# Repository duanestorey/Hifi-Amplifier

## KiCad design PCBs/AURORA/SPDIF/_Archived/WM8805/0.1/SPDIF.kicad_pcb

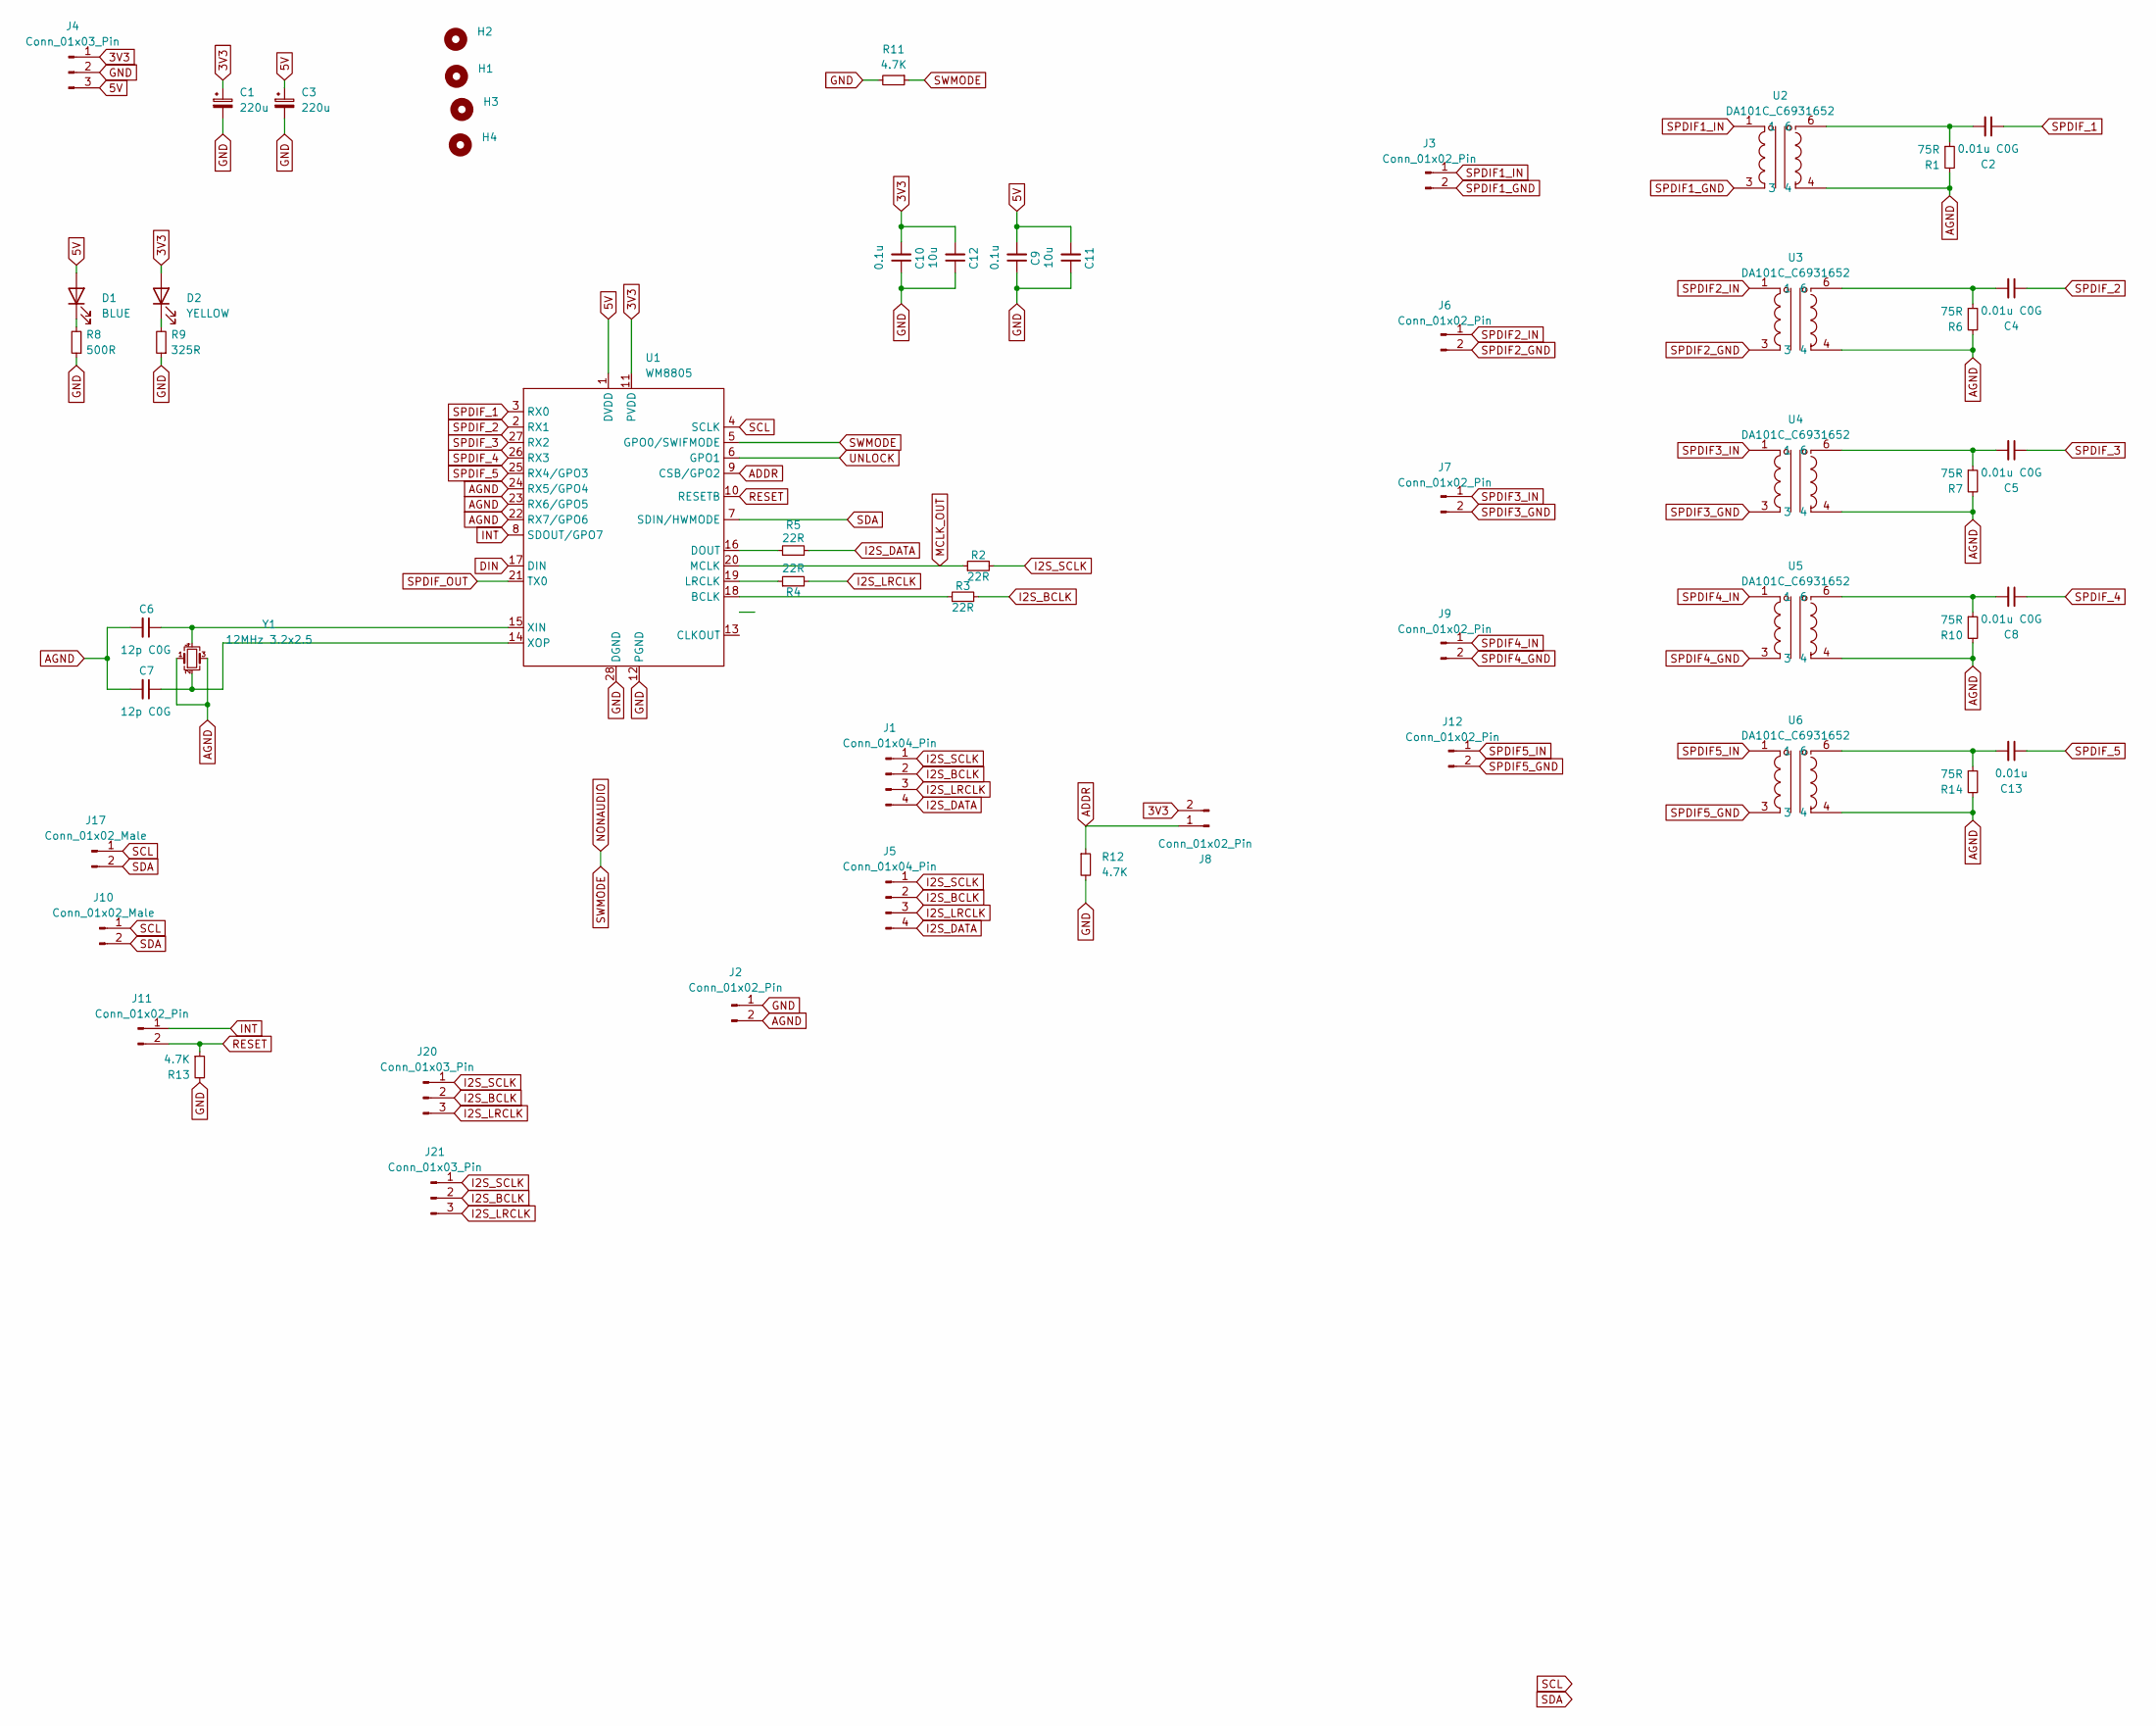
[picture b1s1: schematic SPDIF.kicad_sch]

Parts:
C1, C3: 220u; CP_Radial_D6.3mm_P2.50mm
C2, C4, C5, C8: 0.01u C0G; C_0805_2012Metric_Pad1.18x1.45mm_HandSolder; Mouser 791-0805N103G250CT
C6, C7: 12p C0G; C_0805_2012Metric_Pad1.18x1.45mm_HandSolder; Mouser 603-CC805FRNPO9BN120
C9, C10: 0.1u; C_0805_2012Metric_Pad1.18x1.45mm_HandSolder
C11, C12: 10u; C_1206_3216Metric_Pad1.33x1.80mm_HandSolder
C13: 0.01u; C_0805_2012Metric_Pad1.18x1.45mm_HandSolder; Mouser C0G
D1: BLUE; LED_0805_2012Metric_Pad1.15x1.40mm_HandSolder
D2: YELLOW; LED_0805_2012Metric_Pad1.15x1.40mm_HandSolder
H1, H2, H3, H4: MountingHole; MountingHole_3.2mm_M3_DIN965_Pad_TopOnly
J1: Conn_01x04_Pin; JST_PH_B4B-PH-K_1x04_P2.00mm_Vertical
J2, J8: Conn_01x02_Pin; PinHeader_1x02_P2.54mm_Vertical
J3, J6, J7, J9, J12: Conn_01x02_Pin; JST_XH_B2B-XH-A_1x02_P2.50mm_Vertical
J4, J20, J21: Conn_01x03_Pin; JST_PH_B3B-PH-K_1x03_P2.00mm_Vertical
J5: Conn_01x04_Pin; PinHeader_1x04_P2.54mm_Vertical
J10, J17: Conn_01x02_Male; JST_PH_B2B-PH-K_1x02_P2.00mm_Vertical
J11: Conn_01x02_Pin; JST_PH_B2B-PH-K_1x02_P2.00mm_Vertical
R1, R6, R7, R10, R14: 75R; R_0603_1608Metric_Pad0.98x0.95mm_HandSolder; Mouser 71-CRCW0603-75-E3
R2, R3, R4, R5: 22R; R_0805_2012Metric_Pad1.20x1.40mm_HandSolder
R8: 500R; R_0603_1608Metric_Pad0.98x0.95mm_HandSolder
R9: 325R; R_0603_1608Metric_Pad0.98x0.95mm_HandSolder
R11, R12, R13: 4.7K; R_0603_1608Metric_Pad0.98x0.95mm_HandSolder
U1: WM8805; SSOP-28_5.3x10.2mm_P0.65mm
U2, U3, U4, U5, U6: DA101C_C6931652; XFMR-TH_4P-L9.5-W9.0-P5.08-LS10.2_C9900096976; LCSC Part C6931652
Y1: 12MHz 3.2x2.5; Crystal_SMD_SeikoEpson_FA238-4Pin_3.2x2.5mm; Mouser 520-120-8-33B2CKMTR3

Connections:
3V3: C1.1, C10.2, C12.2, D2.2 (A), J4.1, J8.2, U1.11 (PVDD)
5V: C3.1, C9.2, C11.2, D1.2 (A), J4.3, U1.1 (DVDD)
ADDR: J8.1, R12.1, U1.9 (CSB/GPO2)
AGND: C6.2, C7.2, J2.2, R1.2, R6.2, R7.2, R10.2, R14.2, U1.22 (RX7/GPO6), U1.23 (RX6/GPO5), U1.24 (RX5/GPO4), U2.4, U3.4, U4.4, U5.4, U6.4, Y1.1, Y1.3
DIN: U1.17 (DIN)
GND: C1.2, C3.2, C9.1, C10.1, C11.1, C12.1, J2.1, J4.2, R8.1, R9.1, R11.2, R12.2, R13.2, U1.12 (PGND), U1.28 (DGND)
I2S_BCLK: J1.2, J5.2, J20.2, J21.2, R3.2
I2S_DATA: J1.4, J5.4, R5.2
I2S_LRCLK: J1.3, J5.3, J20.3, J21.3, R4.2
I2S_SCLK: J1.1, J5.1, J20.1, J21.1, R2.2
INT: J11.1, U1.8 (SDOUT/GPO7)
MCLK_OUT: R2.1, U1.20 (MCLK)
NONAUDIO: R11.1, U1.5 (GPO0/SWIFMODE)
unnamed: C2.2, R1.1, U2.6
unnamed: C4.2, R6.1, U3.6
unnamed: C5.2, R7.1, U4.6
unnamed: C8.2, R10.1, U5.6
unnamed: C13.2, R14.1, U6.6
unnamed: D1.1 (K), R8.2
unnamed: D2.1 (K), R9.2
unnamed: R3.1, U1.18 (BCLK)
unnamed: R5.1, U1.16 (DOUT)
unnamed: R4.1, U1.19 (LRCLK)
unnamed: C6.1, U1.15 (XIN), Y1.4
unnamed: C7.1, U1.14 (XOP), Y1.2
RESET: J11.2, R13.1, U1.10 (RESETB)
SCL: J10.1, J17.1, U1.4 (SCLK)
SDA: J10.2, J17.2, U1.7 (SDIN/HWMODE)
SPDIF1_GND: J3.2, U2.3
SPDIF1_IN: J3.1, U2.1
SPDIF2_GND: J6.2, U3.3
SPDIF2_IN: J6.1, U3.1
SPDIF3_GND: J7.2, U4.3
SPDIF3_IN: J7.1, U4.1
SPDIF4_GND: J9.2, U5.3
SPDIF4_IN: J9.1, U5.1
SPDIF5_GND: J12.2, U6.3
SPDIF5_IN: J12.1, U6.1
SPDIF_1: C2.1, U1.3 (RX0)
SPDIF_2: C4.1, U1.2 (RX1)
SPDIF_3: C5.1, U1.27 (RX2)
SPDIF_4: C8.1, U1.26 (RX3)
SPDIF_5: C13.1, U1.25 (RX4/GPO3)
SPDIF_OUT: U1.21 (TX0)
UNLOCK: U1.6 (GPO1)

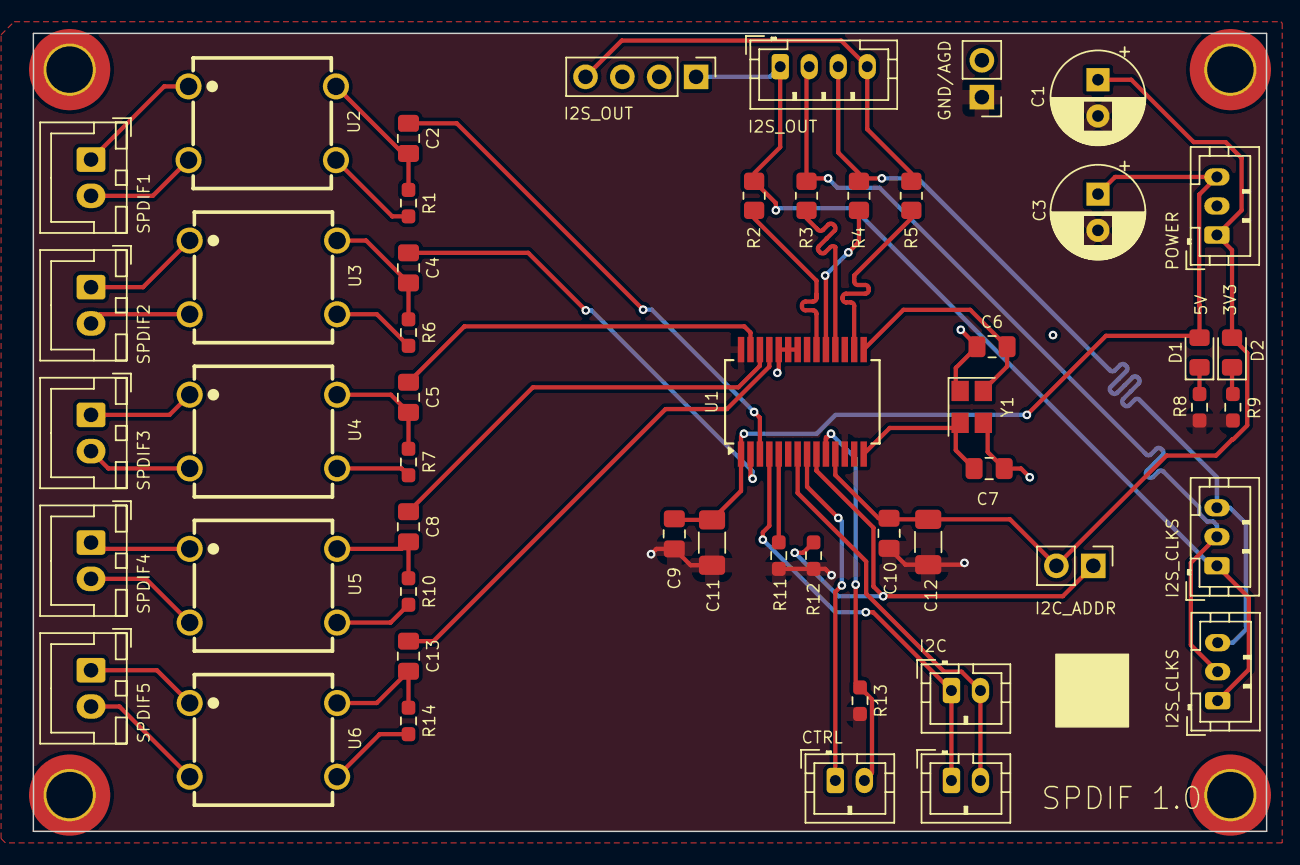
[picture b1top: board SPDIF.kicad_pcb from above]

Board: 4 copper layers, 85.0 x 55.0 mm, 55 parts (0 on the bottom side), 42 nets.

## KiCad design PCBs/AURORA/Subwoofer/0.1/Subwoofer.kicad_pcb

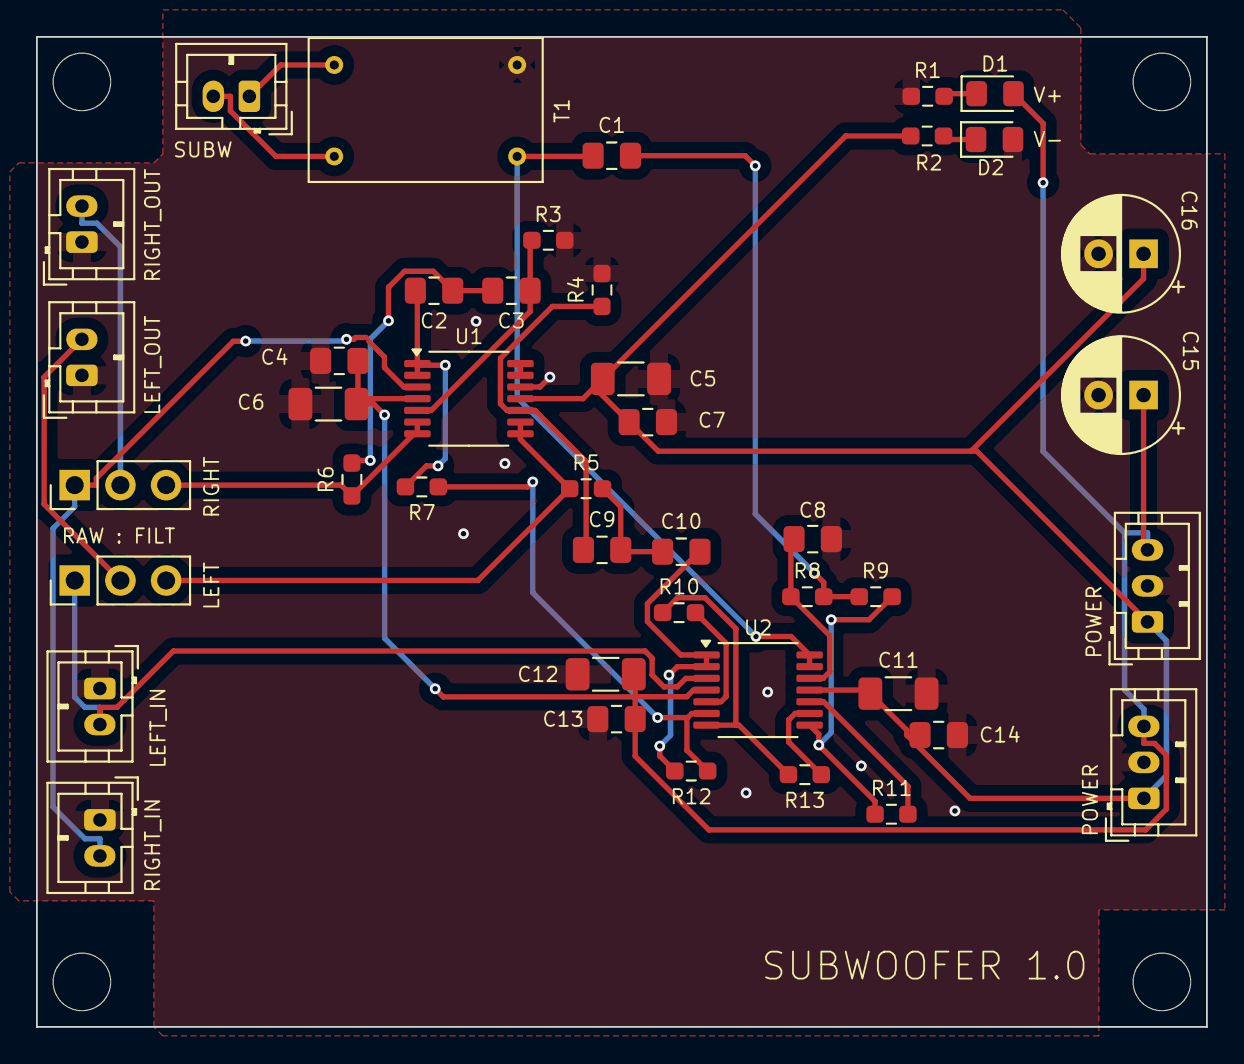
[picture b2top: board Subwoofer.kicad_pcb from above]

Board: 2 copper layers, 65.0 x 55.0 mm, 47 parts (0 on the bottom side), 29 nets.

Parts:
C1, C2, C3, C9, C10: 200N C0G; C_0805_2012Metric_Pad1.18x1.45mm_HandSolder
C4, C7, C13, C14: 0.1U; C_0805_2012Metric_Pad1.18x1.45mm_HandSolder
C5, C6, C11, C12: 10U; C_1206_3216Metric_Pad1.33x1.80mm_HandSolder
C8: 91N C0G; C_0805_2012Metric_Pad1.18x1.45mm_HandSolder
C15, C16: 470u; CP_Radial_D6.3mm_P2.50mm
D1: YELLOW; LED_0805_2012Metric_Pad1.15x1.40mm_HandSolder
D2: BLUE; LED_0805_2012Metric_Pad1.15x1.40mm_HandSolder
H1, H2, H3, H4: MountingHole; MountingHole_3.2mm_M3
J1, J2, J3, J7, J9: Conn_01x02_Pin; JST_PH_B2B-PH-K_1x02_P2.00mm_Vertical
J4, J5: Conn_01x03_Pin; PinHeader_1x03_P2.54mm_Vertical
J6, J8: Conn_01x03_Male; JST_PH_B3B-PH-K_1x03_P2.00mm_Vertical
R1: 1.25K; R_0603_1608Metric_Pad0.98x0.95mm_HandSolder
R2: 1K; R_0603_1608Metric_Pad0.98x0.95mm_HandSolder
R3, R4, R5, R6: 6.8K; R_0603_1608Metric_Pad0.98x0.95mm_HandSolder
R7: 25k; R_0603_1608Metric_Pad0.98x0.95mm_HandSolder
R8: 20K; R_0603_1608Metric_Pad0.98x0.95mm_HandSolder
R9: 11K; R_0603_1608Metric_Pad0.98x0.95mm_HandSolder
R10, R11, R12, R13: 25K; R_0603_1608Metric_Pad0.98x0.95mm_HandSolder
T1: Transformer_Audio; DA101C
U1, U2: Opamp_Quad; TSSOP-14_4.4x5mm_P0.65mm

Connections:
AGND: C4.2, C5.2, C6.2, C7.2, C8.1, C11.2, C12.2, C13.2, C14.2, C15.2, C16.2, D2.2 (A), J2.1, J3.1, J6.2, J7.1, J8.2, J9.1, R1.1, R3.2, R4.2, T1.2 (AB), U1.12 (+)
LEFT_FILT: J5.3, R5.1, U1.8, U1.9 (-)
LEFT_IN: J5.1, J7.2, U2.3 (+)
LEFT_OUT: J3.2, J5.2
unnamed: C1.2, R8.2, R9.1
unnamed: C2.1, C3.2, R6.2
unnamed: C9.2, C10.1, R5.2
unnamed: D1.1 (K), R1.2
unnamed: D2.1 (K), R2.2
unnamed: R10.1, R13.2, U2.7
unnamed: R9.2, R11.1, U2.8
unnamed: C2.2, R7.2, U1.1, U1.2 (-)
unnamed: C3.1, R3.1, U1.5 (+)
unnamed: C9.1, R4.1, U1.10 (+)
unnamed: U1.13 (-), U1.14
unnamed: C10.2, R12.2, U2.1, U2.2 (-)
unnamed: R10.2, U2.5 (+)
unnamed: R7.1, R12.1, U2.6 (-)
unnamed: R11.2, U2.10 (+)
unnamed: R13.1, U2.9 (-)
unnamed: C8.2, R8.1, U2.12 (+)
RIGHT_FILT: J4.3, R6.1, U1.6 (-), U1.7
RIGHT_IN: J4.1, J9.2, U1.3 (+)
RIGHT_OUT: J2.2, J4.2
SUBW: C1.1, T1.1 (AA), U2.13 (-), U2.14
SUBWN: J1.1, T1.3 (SA)
SUBWP: J1.2, T1.4 (SB)
V+: C4.1, C6.1, C12.1, C13.1, C15.1, D1.2 (A), J6.3, J8.3, U1.4 (V+), U2.4 (V+)
V-: C5.1, C7.1, C11.1, C14.1, C16.1, J6.1, J8.1, R2.1, U1.11 (V-), U2.11 (V-)

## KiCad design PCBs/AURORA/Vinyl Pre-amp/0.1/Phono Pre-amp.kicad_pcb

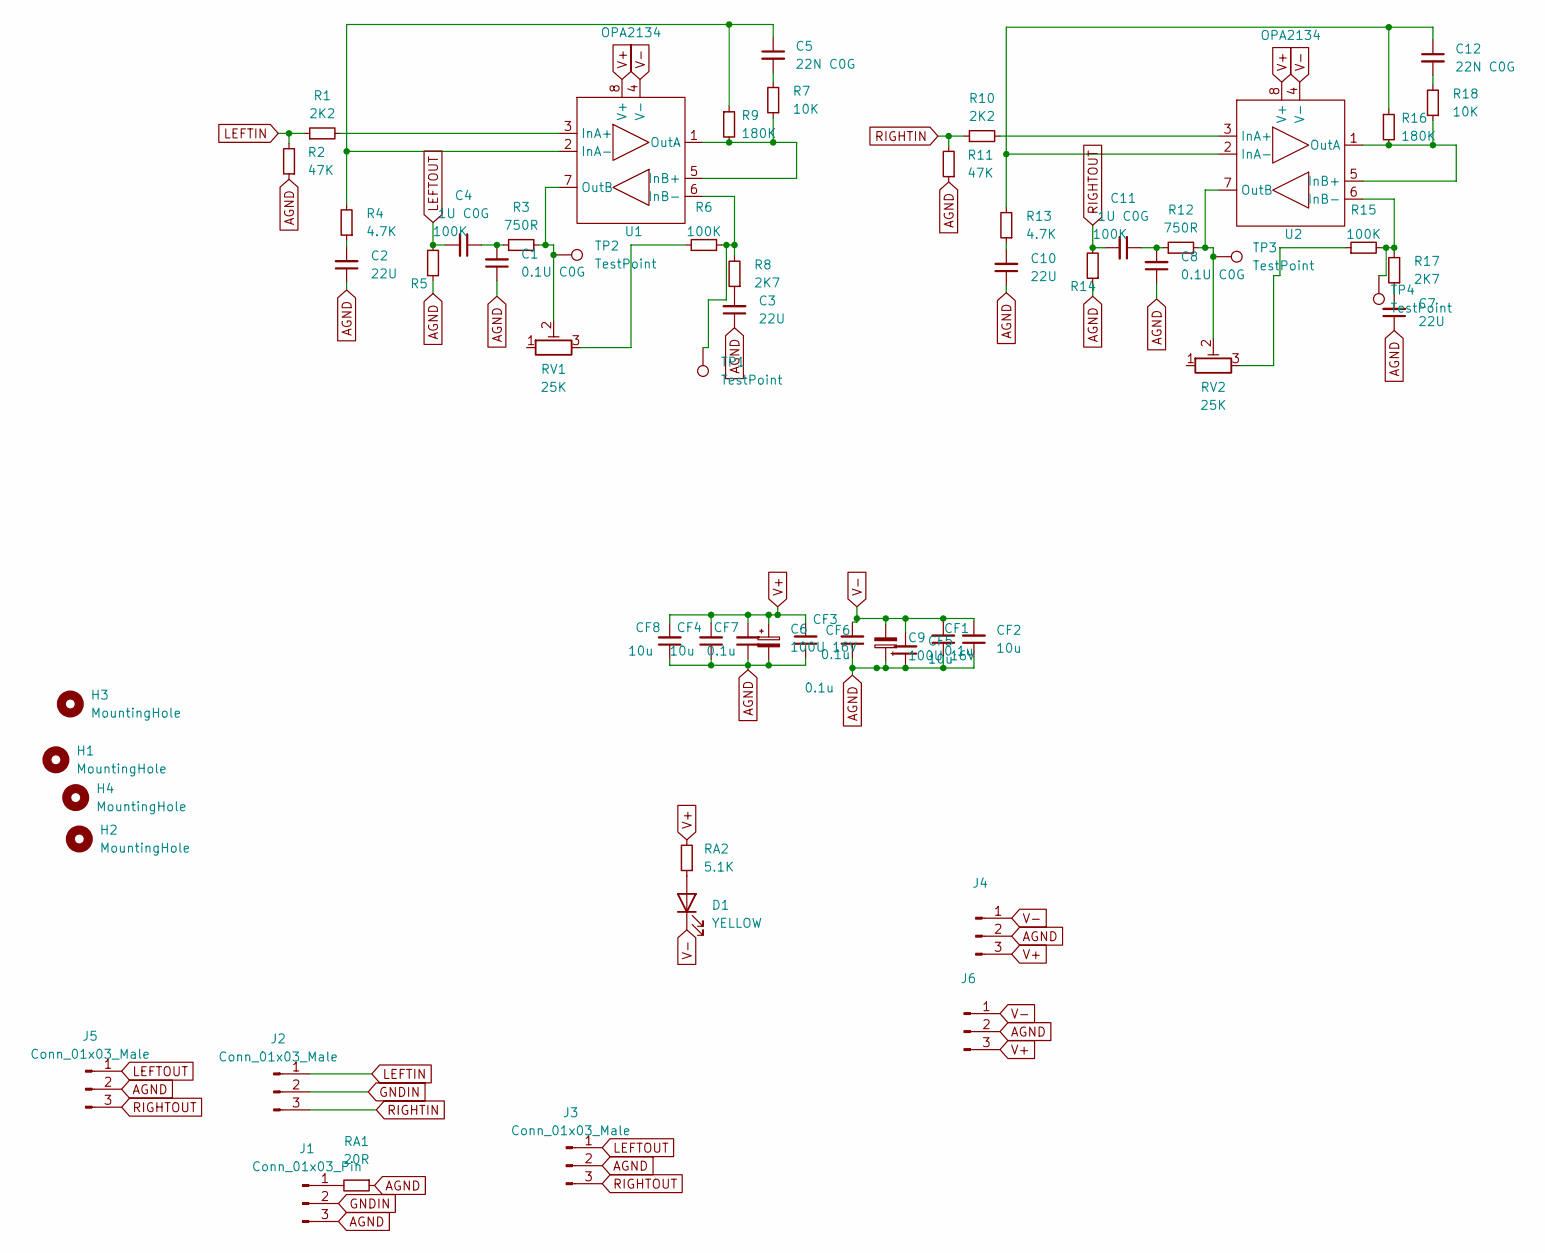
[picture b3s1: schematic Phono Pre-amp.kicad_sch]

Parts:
C1, C8: 0.1U C0G; C_1206_3216Metric_Pad1.33x1.80mm_HandSolder
C2, C3, C7, C10: 22U; CP_Radial_D6.3mm_P2.50mm
C4, C11: 1U C0G; C_Rect_L7.2mm_W11.0mm_P5.00mm_FKS2_FKP2_MKS2_MKP2
C5, C12: 22N C0G; C_0805_2012Metric_Pad1.18x1.45mm_HandSolder
C6, C9: 100U 16V; CP_Radial_D6.3mm_P2.50mm
CF1, CF3, CF6, CF7: 0.1u; C_0805_2012Metric_Pad1.18x1.45mm_HandSolder
CF2, CF4, CF5, CF8: 10u; C_1206_3216Metric_Pad1.33x1.80mm_HandSolder
D1: YELLOW; LED_0805_2012Metric_Pad1.15x1.40mm_HandSolder
H1, H2, H3, H4: MountingHole; MountingHole_3.2mm_M3
J1: Conn_01x03_Pin; PinHeader_1x03_P2.54mm_Vertical
J2, J4, J5, J6: Conn_01x03_Male; JST_PH_B3B-PH-K_1x03_P2.00mm_Vertical
J3: Conn_01x03_Male; PinHeader_1x03_P2.54mm_Vertical
R1, R10: 2K2; R_0805_2012Metric_Pad1.20x1.40mm_HandSolder
R2, R11: 47K; R_0805_2012Metric_Pad1.20x1.40mm_HandSolder
R3, R12: 750R; R_0805_2012Metric_Pad1.20x1.40mm_HandSolder
R4, R13: 4.7K; R_0805_2012Metric_Pad1.20x1.40mm_HandSolder
R5, R6, R14, R15: 100K; R_0805_2012Metric_Pad1.20x1.40mm_HandSolder
R7, R18: 10K; R_0805_2012Metric_Pad1.20x1.40mm_HandSolder
R8, R17: 2K7; R_0805_2012Metric_Pad1.20x1.40mm_HandSolder
R9, R16: 180K; R_0805_2012Metric_Pad1.20x1.40mm_HandSolder
RA1: 20R; R_0603_1608Metric
RA2: 5.1K; R_0603_1608Metric
RV1, RV2: 25K; Potentiometer_Bourns_3296W_Vertical
TP1, TP2, TP3, TP4: TestPoint; TestPoint_THTPad_1.5x1.5mm_Drill0.7mm
U1, U2: OPA2134; DIP-8_W7.62mm_Socket

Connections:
AGND: C1.1, C2.1, C3.1, C6.2, C7.1, C8.1, C9.1, C10.1, CF1.1, CF2.1, CF3.1, CF4.1, CF5.1, CF6.1, CF7.1, CF8.1, J1.3, J3.2, J4.2, J5.2, J6.2, R2.1, R5.1, R11.1, R14.1, RA1.1
GNDIN: J1.2, J2.2
LEFTIN: J2.1, R1.1, R2.2
LEFTOUT: C4.2, J3.1, J5.1, R5.2
unnamed: C1.2, C4.1, R3.1
unnamed: C2.2, R4.1
unnamed: C3.2, R8.1
unnamed: C5.2, R7.2
unnamed: C7.2, R17.1
unnamed: C10.2, R13.1
unnamed: C8.2, C11.1, R12.1
unnamed: C12.2, R18.2
unnamed: D1.2 (A), RA2.1
unnamed: J1.1, RA1.2
unnamed: R6.1, RV1.3
unnamed: R15.1, RV2.3
unnamed: R1.2, U1.3 (InA+)
unnamed: C5.1, R4.2, R9.1, U1.2 (InA-)
unnamed: R7.1, R9.2, U1.1 (OutA), U1.5 (InB+)
unnamed: R6.2, R8.2, TP1.1, U1.6 (InB-)
unnamed: R3.2, RV1.2, TP2.1, U1.7 (OutB)
unnamed: R10.2, U2.3 (InA+)
unnamed: C12.1, R13.2, R16.1, U2.2 (InA-)
unnamed: R16.2, R18.1, U2.1 (OutA), U2.5 (InB+)
unnamed: R15.2, R17.2, TP4.1, U2.6 (InB-)
unnamed: R12.2, RV2.2, TP3.1, U2.7 (OutB)
RIGHTIN: J2.3, R10.1, R11.2
RIGHTOUT: C11.2, J3.3, J5.3, R14.2
V+: C6.1, CF3.2, CF4.2, CF7.2, CF8.2, J4.3, J6.3, RA2.2, U1.8 (V+), U2.8 (V+)
V-: C9.2, CF1.2, CF2.2, CF5.2, CF6.2, D1.1 (K), J4.1, J6.1, U1.4 (V-), U2.4 (V-)

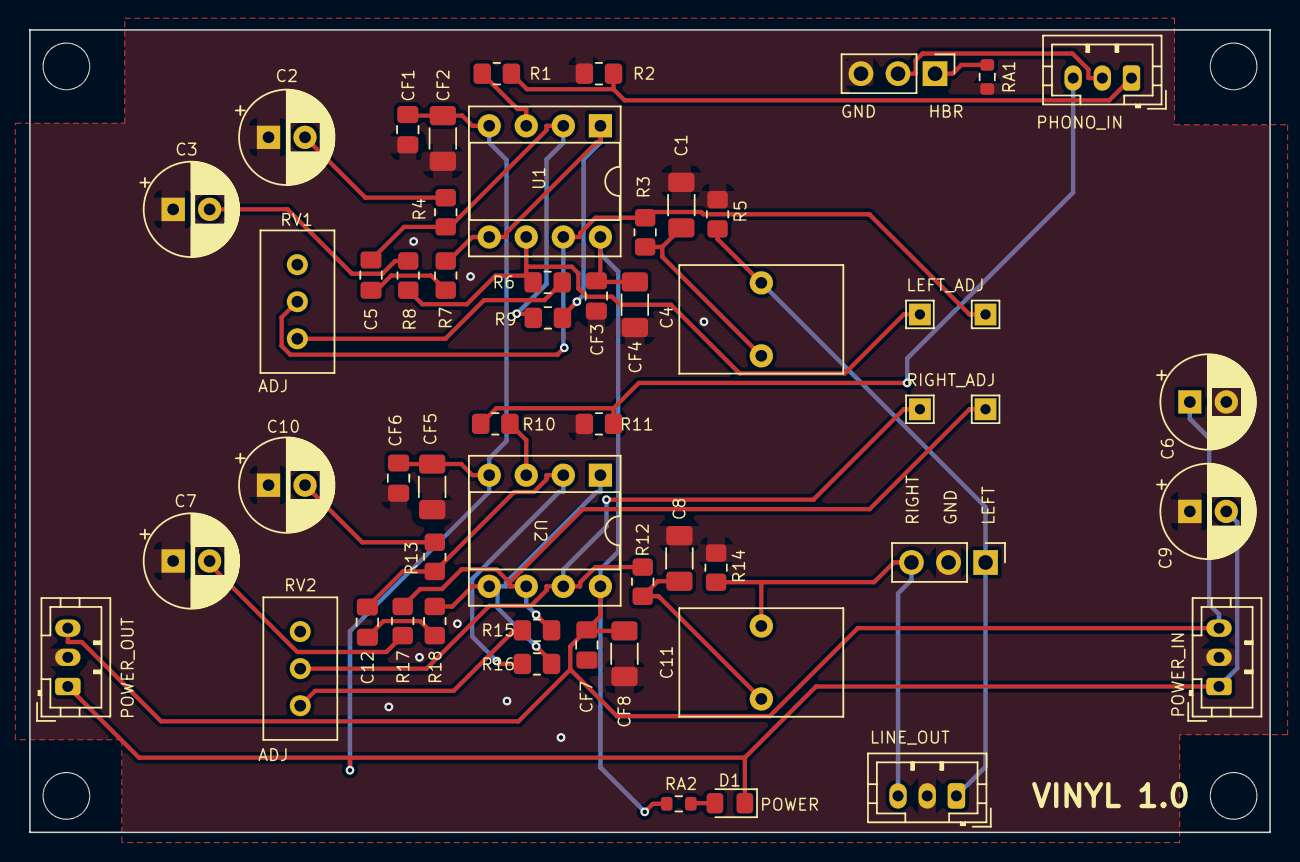
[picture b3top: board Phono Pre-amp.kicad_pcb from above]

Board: 2 copper layers, 85.0 x 55.0 mm, 59 parts (0 on the bottom side), 30 nets.

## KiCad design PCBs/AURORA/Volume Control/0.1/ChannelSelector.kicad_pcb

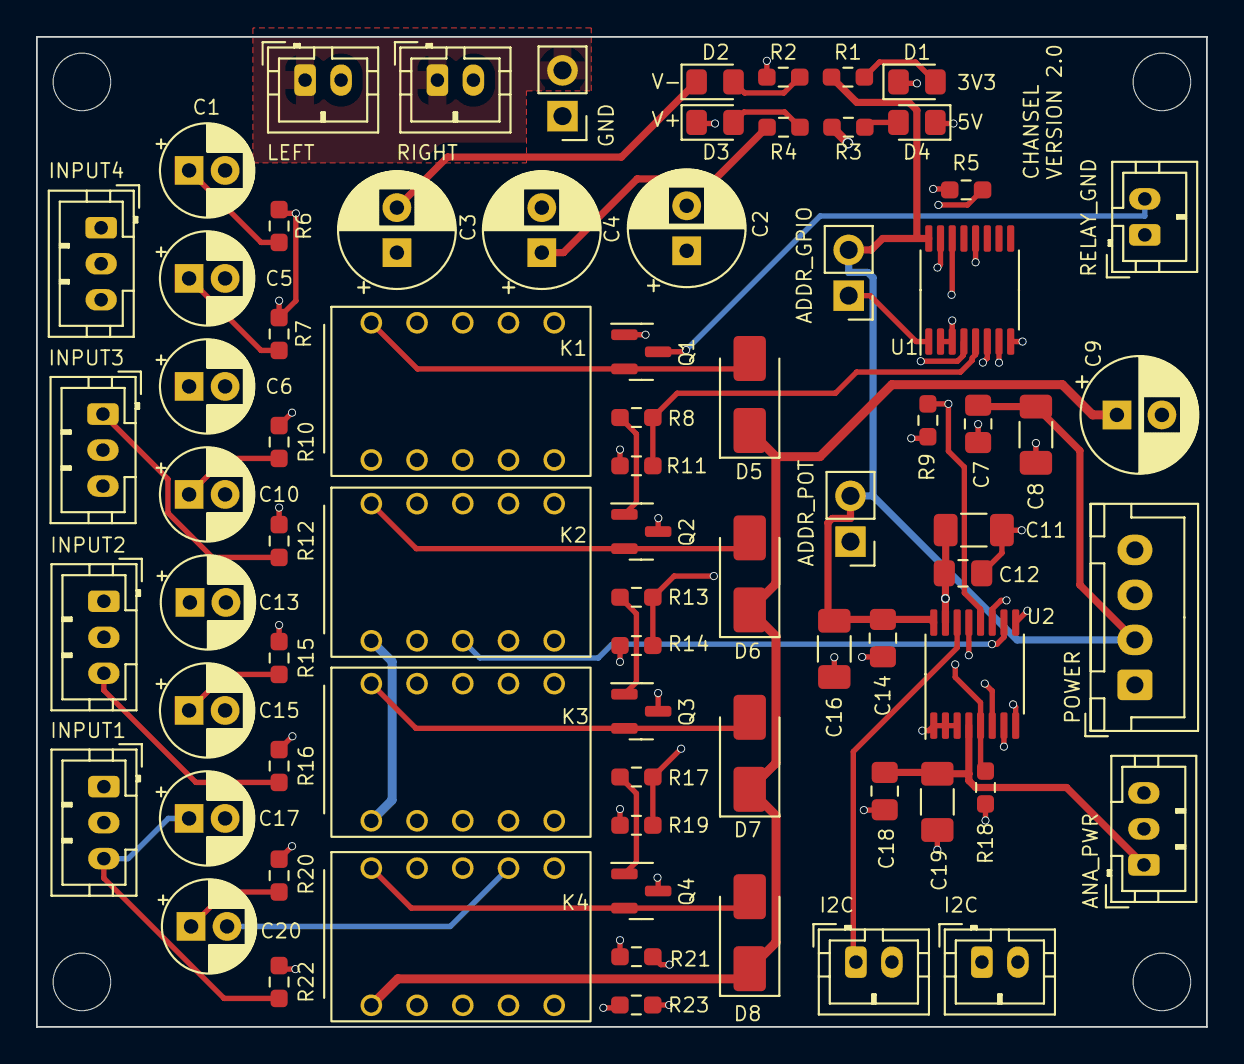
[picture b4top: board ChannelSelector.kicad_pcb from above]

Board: 4 copper layers, 65.0 x 55.0 mm, 79 parts (0 on the bottom side), 49 nets.

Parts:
C1, C5, C6, C10, C13, C15, C17, C20: 10u; CP_Radial_D5.0mm_P2.00mm
C2, C3, C4, C9: 470u; CP_Radial_D6.3mm_P2.50mm
C7, C12, C14, C18: 0.1U; C_0805_2012Metric_Pad1.18x1.45mm_HandSolder
C8, C16: 10U; C_1206_3216Metric_Pad1.33x1.80mm_HandSolder
C11, C19: 47U; C_1206_3216Metric_Pad1.33x1.80mm_HandSolder
D1, D3: YELLOW; LED_0805_2012Metric_Pad1.15x1.40mm_HandSolder
D2, D4: BLUE; LED_0805_2012Metric_Pad1.15x1.40mm_HandSolder
D5, D6, D7, D8: 1N4001; D_SMA
H1, H2, H3, H4: MountingHole; MountingHole_3.2mm_M3
J1, J2, J4: Conn_01x02_Pin; JST_PH_B2B-PH-K_1x02_P2.00mm_Vertical
J3: Conn_01x02_Male; PinHeader_1x02_P2.54mm_Vertical
J5, J7, J10, J11: Conn_01x03_Pin; JST_PH_B3B-PH-K_1x03_P2.00mm_Vertical
J6, J8: Conn_01x02_Pin; PinHeader_1x02_P2.54mm_Vertical
J9: Conn_01x04_Pin; JST_XH_B4B-XH-A_1x04_P2.50mm_Vertical
J12: Conn_01x03_Male; JST_PH_B3B-PH-K_1x03_P2.00mm_Vertical
J13, J14: Conn_01x02_Male; JST_PH_B2B-PH-K_1x02_P2.00mm_Vertical
K1, K2, K3, K4: EA2-5NU; KEMET EA2
Q1, Q2, Q3, Q4: BC859; SOT-23
R1: 430R; R_0603_1608Metric_Pad0.98x0.95mm_HandSolder
R2: 1k; R_0603_1608Metric_Pad0.98x0.95mm_HandSolder
R3: 670R; R_0603_1608Metric_Pad0.98x0.95mm_HandSolder
R4: 1.25k; R_0603_1608Metric_Pad0.98x0.95mm_HandSolder
R5, R9, R11, R14, R18, R19, R23: 4.7K; R_0603_1608Metric_Pad0.98x0.95mm_HandSolder
R6, R7, R10, R12, R15, R16, R20, R22: 50k; R_0603_1608Metric_Pad0.98x0.95mm_HandSolder
R8, R13, R17, R21: 1K; R_0603_1608Metric_Pad0.98x0.95mm_HandSolder
U1: TCA9554PW; TSSOP-16_4.4x5mm_P0.65mm
U2: DS1882E; TSSOP-16_4.4x5mm_P0.65mm

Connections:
3V3: C2.1, C7.1, C8.1, C14.1, C16.1, J6.2, J8.2, J9.2, R1.1, U1.16 (VDD), U2.16 (VDD)
5V: C9.1, D5.1 (K), D6.1 (K), D7.1 (K), D8.1 (K), J9.4, K1.1, K2.1, K3.1, K4.1, R3.1
A0: J8.1, R18.1, U2.5 (A0)
A0_2: J6.1, R5.1, U1.1 (A0)
AGND: C11.2, C12.2, C18.2, C19.2, D3.1 (K), J3.1, J5.2, J7.2, J10.2, J11.2, J12.2, R2.1, R6.1, R7.1, R10.1, R12.1, R15.1, R16.1, R20.1, R22.1, U2.7 (L0), U2.9 (L1)
CE: R9.2, U1.12 (P7), U2.12 (~CE)
FL_AIN: K1.9, K2.9, K3.9, K4.9, U2.8 (H0)
FL_AV: J1.2, U2.6 (W0)
FR_AIN: K1.4, K2.4, K3.4, K4.4, U2.10 (H1)
FR_AV: J2.2, U2.11 (W1)
GND: C2.2, C3.1, C4.2, C7.2, C8.2, C9.2, C14.2, C16.2, D1.1 (K), D4.1 (K), J4.1, J9.1, J9.3, R5.2, R9.1, R11.1, R14.1, R18.2, R19.1, R23.1, U1.2 (A1), U1.3 (A2), U1.8 (GND), U2.1 (GND), U2.2 (A2), U2.3 (A1)
GND_OUT: J1.1, J2.1, J3.2
unnamed: D1.2 (A), R1.2
unnamed: D2.2 (A), R2.2
unnamed: D3.2 (A), R4.2
unnamed: D4.2 (A), R3.2
unnamed: D5.2 (A), K1.12, Q1.2 (E)
unnamed: D6.2 (A), K2.12, Q2.2 (E)
unnamed: D7.2 (A), K3.12, Q3.2 (E)
unnamed: D8.2 (A), K4.12, Q4.2 (E)
unnamed: C1.1, J5.1, R6.2
unnamed: C5.1, J5.3, R7.2
unnamed: C6.1, J7.1, R12.2
unnamed: C10.1, J7.3, R10.2
unnamed: C15.1, J10.1, R15.2
unnamed: C13.1, J10.3, R16.2
unnamed: C20.1, J11.1, R20.2
unnamed: C17.1, J11.3, R22.2
unnamed: Q1.1 (B), R21.2
unnamed: Q2.1 (B), R8.2
unnamed: Q3.1 (B), R13.2
unnamed: Q4.1 (B), R17.2
RCA1: R17.1, R19.2, U1.7 (P3)
RCA1_L: C20.2, K4.8
RCA1_R: C17.2, K4.5
RCA2: R13.1, R14.2, U1.6 (P2)
RCA2_L: C15.2, K3.8
RCA2_R: C13.2, K3.5
RCA3: R8.1, R11.2, U1.5 (P1)
RCA3_L: C6.2, K2.8
RCA3_R: C10.2, K2.5
RCA4: R21.1, R23.2, U1.4 (P0)
RCA4_L: C1.2, K1.8
RCA4_R: C5.2, K1.5
REL_GND: J4.2, Q1.3 (C), Q2.3 (C), Q3.3 (C), Q4.3 (C)
SCL: J13.1, J14.1, U1.14 (SCL), U2.14 (SCL)
SDA: J13.2, J14.2, U1.15 (SDA), U2.13 (SDA)
V+: C4.1, C11.1, C12.1, J12.3, R4.1, U2.15 (VCC)
V-: C3.2, C18.1, C19.1, D2.1 (K), J12.1, U2.4 (V-)

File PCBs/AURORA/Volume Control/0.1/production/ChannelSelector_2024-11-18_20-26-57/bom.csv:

Designator,Footprint,Quantity,Value,LCSC Part #
"C1, C10, C13, C15, C17, C20, C5, C6",CP_Radial_D5.0mm_P2.00mm,8,10u,
"C11, C19",1206,2,47U,
"C12, C14, C18, C7",0805,4,0.1U,
"C16, C8",1206,2,10U,
"C2, C3, C4, C9",CP_Radial_D6.3mm_P2.50mm,4,470u,
"D1, D3",0805,2,YELLOW,
"D2, D4",0805,2,BLUE,
"D5, D6, D7, D8",D_SMA,4,1N4001,
"H1, H2, H3, H4",MountingHole_3.2mm_M3,4,MountingHole,
"J1, J2, J4",JST_PH_B2B-PH-K_1x02_P2.00mm_Vertical,3,Conn_01x02_Pin,
"J10, J11, J5, J7",JST_PH_B3B-PH-K_1x03_P2.00mm_Vertical,4,Conn_01x03_Pin,
J12,JST_PH_B3B-PH-K_1x03_P2.00mm_Vertical,1,Conn_01x03_Male,
"J13, J14",JST_PH_B2B-PH-K_1x02_P2.00mm_Vertical,2,Conn_01x02_Male,
J3,PinHeader_1x02_P2.54mm_Vertical,1,Conn_01x02_Male,
"J6, J8",PinHeader_1x02_P2.54mm_Vertical,2,Conn_01x02_Pin,
J9,JST_XH_B4B-XH-A_1x04_P2.50mm_Vertical,1,Conn_01x04_Pin,
"K1, K2, K3, K4",KEMET EA2,4,EA2-5NU,
"Q1, Q2, Q3, Q4",SOT-23,4,BC859,
R1,0603,1,430R,
"R10, R12, R15, R16, R20, R22, R6, R7",0603,8,50k,
"R11, R14, R18, R19, R23, R5, R9",0603,7,4.7K,
"R13, R17, R2, R21, R8",0603,5,1K,
R3,0603,1,670R,
R4,0603,1,1.25k,
U1,TSSOP-16_4.4x5mm_P0.65mm,1,TCA9554PW,
U2,TSSOP-16_4.4x5mm_P0.65mm,1,DS1882E,
